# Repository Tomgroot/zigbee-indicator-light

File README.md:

# ESP32 Zigbee Indicator Light

This project implements a Zigbee Color Dimmable Light using ESP32-C6/H2 and an addressable LED (WS2812).

## Features
- Zigbee 3.0 Router
- On/Off, Level (Brightness), and Color (Hue/Saturation) control
- Compatible with Home Assistant (ZHA, Zigbee2MQTT)
- Factory Reset via Boot Button (Hold for 3s)

## Hardware
- **ESP32-C6 or ESP32-H2** (e.g., DevKitM-1)
- **LED**: WS2812/NeoPixel on **GPIO 8** (Default for onboard LED on many devkits)
- **Button**: Boot button on **GPIO 9** (for factory reset)

## Usage
1. Build and Flash:
   ```bash
   idf.py build flash monitor
   ```
2. Hold BOOT button for 3 seconds to reset/pairing mode if needed.
3. Join your Zigbee network.
4. Control via Home Assistant (Light entity).

## Dependencies
- `espressif/esp-zigbee-lib`
- `espressif/led_strip`

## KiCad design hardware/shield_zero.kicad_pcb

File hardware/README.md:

# Import the PCB into EasyEDA Pro

Import this file: `hardware/board_routed.kicad_pcb`. It has all parts placed, all traces routed and GND pours on both layers. It is in KiCad 5.1 format, which is the newest EasyEDA Pro imports.

## 1. Import

1. Open EasyEDA Pro and create a new project (or open an existing one).
2. Stay on the **project view** (the start page or the project tree). Do not open a PCB or schematic first.
3. Click **File → Import → KiCad...**
4. Select `hardware/board_routed.kicad_pcb` and confirm.
5. A board appears in the project tree. Double-click its PCB to open it.
6. Use **View → Fit All**.

## 2. After import

1. Rebuild the copper pours: **Tools → Copper Manager... → Rebuild All → Confirm**. The file contains the pour outlines but EasyEDA computes the fill itself.
2. Check that the red/blue traces are all there and that the top edge of the board (ESP32 antenna end) has no copper on either layer.
3. Run **Design → Check DRC**.

Known DRC findings that are fine:

- J1 (USB-C) GND and VBUS pads are 0.10 mm apart. That is the library footprint (LCSC C165948), widely used on JLCPCB.
- Silkscreen overlaps: reference texts overlap each other or pads. JLCPCB trims silk on pads. Move the texts if you like.

## 3. Order

1. Check the LCSC numbers in `bom.csv`. Stock was checked against JLCPCB on 2026-11-03; all parts were in stock (ESP32-C6-MINI-1-N4 C5736265: 3400, WS2812B-B-V6 C52941391: 7725, AP2114H-3.3 C150716: 2858). Re-match in the BOM tool before ordering.
2. In EasyEDA use **Export → PCB Fabrication File(Gerber)** and click **Export Gerber**. On jlcpcb.com upload the zip, turn on PCB Assembly, then upload `bom.csv` and `cpl.csv` instead of the generated files: the KiCad import carries no LCSC numbers, so JLCPCB guesses (it picked the out-of-stock C5453904 for U1 and found nothing for six parts). `cpl.csv` leaves out the screw holes (H1-H4) and TP1. Regenerate it if parts move.

## If something goes wrong

- **KiCad import is not in the menu:** you are inside a PCB or schematic editor. Close it and go to the project view.
- **Import fails or the board is empty:** tell me the error message. As a fallback import `board.kicad_pcb` (parts and nets only, no traces) and use **Route → Auto Router**.
- **Only the outline is needed:** open the PCB editor, then **File → Import → DXF**, choose `board_outline.dxf` (units are mm), layer **Board Outline**.

## Enclosure

- `base_indicator_light.stl` has a solid floor; there is no button. `base.py` regenerates it from commit 62c14d3 (old floor flexure filled). Do not edit the STL and rerun the script, or the edit is lost.
- Download mode: open the enclosure and short the two bare TP1 pads on the PCB bottom while plugging in USB.
- Zigbee factory reset: plug the light in 5 times in a row (firmware counts power-ups).

## JLCPCB order settings

Board: 32.4 x 32.4 mm. If the order form shows another size (70.4 mm was seen), the EasyEDA import added stray geometry: show only the Board Outline layer, delete everything else on it, and re-check before ordering.

| Setting | Value | Note |
|---|---|---|
| Base material / layers | FR-4, 2 | |
| Dimensions | 32.4 x 32.4 mm | must not read 70.4 |
| PCB qty | 5 | |
| Product type | industrial electronics | |
| Different design / delivery format | 1 / single PCB | |
| Thickness | 1.6 mm | |
| Solder mask / silkscreen | green / white | Economic PCBA: white mask only with leaded HASL |
| Material | FR-4 standard Tg (130-135) | |
| Surface finish | Lead-free HASL | TP1 are bare copper pads on the bottom: OSP oxidises there. ENIG is flatter but ~15x the price. NOTE: not the default, change it |
| Outer copper | 1 oz | |
| Via covering | tented | Required: vias must not be exposed near the grounded USB-C shell |
| Min via hole | 0.3 mm | Board vias are 0.4 mm |
| Outline tolerance | +-0.2 mm (regular) | Enclosure gap is 0.3 mm |
| Confirm production file | yes (first order) | NOTE: not the default, change it |
| Mark on PCB | remove mark | May cost extra |
| Electrical test | flying probe, full | |
| Gold fingers, castellated, edge plating, blind slots, UL mark, HIC | no | |

Assembly:

| Setting | Value | Note |
|---|---|---|
| PCBA type | Economic | All parts are on the top side, so Economic is enough and cheaper. Max 50 boards |
| Assembly side / qty | top / 5 | |
| Edge rails / fiducials | added by JLCPCB | |
| Confirm parts placement | yes | Check polarity of D1, D2 (SOD-123), pin 1 of LED1 and orientation of U1 and J1 |
| Parts selection | by customer (self-service) | Extended parts (U1, J1, LED1, D2) carry a fee each |
| Depanel boards and rails before delivery | yes | Leftover tab stubs would eat the 0.3 mm enclosure gap. NOTE: not the default, change it |
| Solder paste | high temp (lead-free) | |
| Stencil/fixture storage, bake, cleaning, tests, photo, coating, special stencil, nitrogen | no | |
| Packaging | antistatic bubble film | |

## Regenerating (not needed for import)

- `python3 build_pcb.py` rewrites `board.kicad_pcb` (parts, nets and placement).
- `python3 route.py <freerouting.jar> <java>` routes it into `board_routed.kicad_pcb`. It needs KiCad 9's python module (`pcbnew`), Freerouting 2.5 and Java 25.
- Do not run `generate.py`; it is outdated.

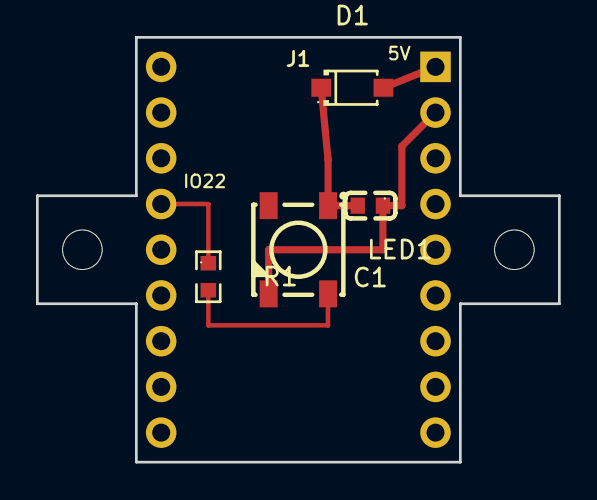
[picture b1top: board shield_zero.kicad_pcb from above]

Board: 2 copper layers, 29.0 x 23.6 mm, 7 parts (0 on the bottom side), 5 nets.

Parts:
C1: 100nF; C0603
D1: 1N4148W; SOD-123F_L2.7-W1.6-LS3.8-RD
H1, H2: M2; MountingHole_2.2mm
J1: ESP32-H2-Zero; H2_Zero_2x9
LED1: SK6812-B; LED-SMD_4P-L5.0-W5.0-TL_WS2812B-B
R1: 470R; R0603

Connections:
5V: D1.2, J1.5V
GND: C1.1, J1.GND, LED1.3
LED_DIN: LED1.4, R1.2
LED_DIN_RAW: J1.IO22, R1.1
VLED: C1.2, D1.1, LED1.1

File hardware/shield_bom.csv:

Comment,Designator,Footprint,JLCPCB Part #,JLC type
SK6812-B,LED1,5050,C5380881,Extended
1N4148W,D1,SOD-123,C81598,Basic
100nF,C1,0603,C14663,Basic
470R,R1,0603,C23179,Basic

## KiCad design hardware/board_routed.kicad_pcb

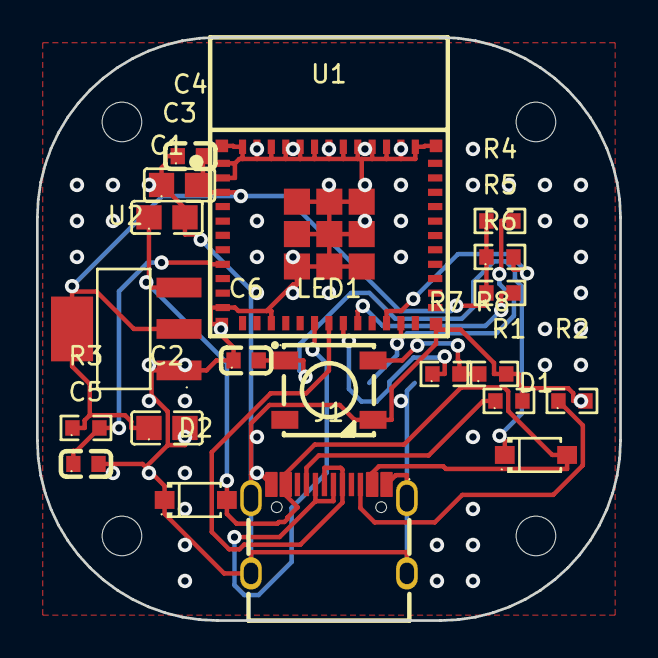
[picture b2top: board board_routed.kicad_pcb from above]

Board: 2 copper layers, 32.4 x 32.4 mm, 25 parts (1 on the bottom side), 14 nets.

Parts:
C1, C3: 10uF; C0805
C2: 22uF; C0805
C4, C6: 100nF; C0603
C5: 1uF; C0603
D1: 1N4148W; SOD-123F_L2.7-W1.6-LS3.8-RD
D2: SMF5.0A; SOD-123F_L2.7-W1.6-LS3.8-RD
H1, H2, H3, H4: M2; MountingHole_2.2mm
J1: USB-C; USB-C_SMD-TYPE-C-31-M-12_1
LED1: WS2812B; LED-SMD_4P-L5.0-W5.0-TL_WS2812B-B
R1, R2: 5.1k; R0603
R3, R4, R5, R6, R8: 10k; R0603
R7: 470R; R0603
TP1: BOOT-GND; TESTPAD_BOOT
U1: ESP32-C6-MINI-1; WIFIM-SMD_61P-L16.6-W13.2-P0.80-ESP32-C6-MINI-1-N4
U2: AP2114H-3.3; SOT-223-3_L6.5-W3.4-P2.30-LS7.0-BR

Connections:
3V3: C2.1, C3.2, C4.2, R3.1, R4.1, R5.1, R6.1, U1.3, U2.2, U2.4
BOOT: R4.2, TP1.1, U1.23
CC1: J1.A5, R1.1
CC2: J1.B5, R2.1
EN: C5.1, R3.2, U1.8
GND: C1.2, C2.2, C3.1, C4.1, C5.2, C6.1, D2.1, J1.1, J1.2, J1.3, J1.4, J1.A1B12, J1.B1A12, LED1.3, R1.2, R2.2, R8.2, TP1.2, U1.1, U1.2, U1.11, U1.14, U1.36, U1.37, U1.38, U1.39, U1.40, U1.41, U1.42, U1.43, U1.44, U1.45, U1.46, U1.47, U1.48, U1.49, U1.50, U1.51, U1.52, U1.53, U2.1
IO8: R5.2, U1.22
IO14: R7.1, U1.19
IO15: R6.2, U1.20
LED_DIN: LED1.4, R7.2, R8.1
USB_DN: J1.A7, J1.B7, U1.17
USB_DP: J1.A6, J1.B6, U1.18
VBUS: C1.1, D1.2, D2.2, J1.A4B9, J1.B4A9, U2.3
VLED: C6.2, D1.1, LED1.1

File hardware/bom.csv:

Comment,Designator,Footprint,JLCPCB Part #（optional）,JLC type
ESP32-C6-MINI-1-N4,U1,ESP32-C6-MINI-1,C5736265,Extended
AP2114H-3.3,U2,SOT-223,C150716,Extended
TYPE-C-31-M-12 (USB-C 16p),J1,USB-C SMD,C165948,Extended
WS2812B-B-V6,LED1,5050,C52941391,Extended
1N4148W,D1,SOD-123,C81598,Basic
SMF5.0A (TVS),D2,SOD-123FL,C151296,Extended
22uF,C2,0805,C45783,Basic
10uF,"C1,C3",0805,C15850,Basic
1uF,C5,0603,C15849,Basic
100nF,"C4,C6",0603,C14663,Basic
10k,"R3,R4,R5,R6,R8",0603,C25804,Basic
5.1k,"R1,R2",0603,C23186,Basic
470R,R7,0603,C23179,Basic

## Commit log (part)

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2025-12-13 First version of indicator light
2026-06-03 Working RGB led version
